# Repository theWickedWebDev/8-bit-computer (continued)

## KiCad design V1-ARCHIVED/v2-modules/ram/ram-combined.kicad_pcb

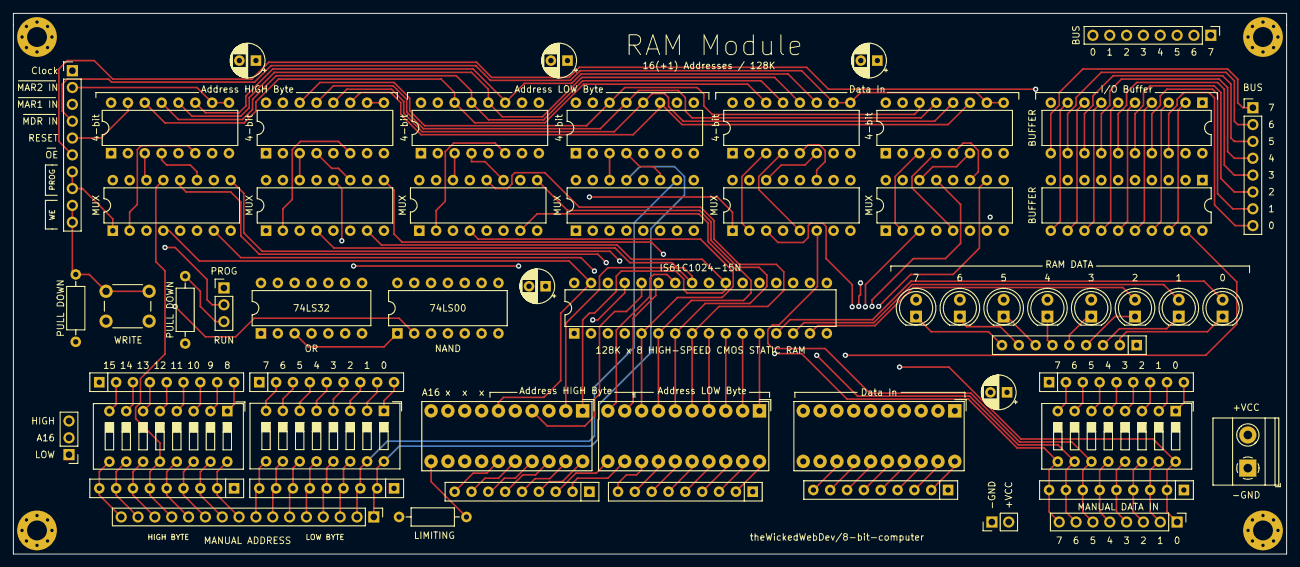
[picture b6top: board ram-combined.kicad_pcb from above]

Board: 4 copper layers, 192.0 x 81.5 mm, 59 parts (0 on the bottom side), 159 nets.

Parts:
BAR1, BAR2, BAR3: HDSP-4830_2; HDSP-4830
C1, C2, C3, C4, C5: CP1_Small; CP_Radial_D5.0mm_P2.50mm
D1, D2, D3, D4, D5, D6, D7, D8: LED; LED_D5.0mm
J1, J2, J8: Conn_01x08; PinHeader_1x08_P2.54mm_Vertical
J3: Conn_01x10; PinHeader_1x10_P2.54mm_Vertical
J4: Conn_01x02; PinHeader_1x02_P2.54mm_Vertical
J5: Screw_Terminal_01x02; TerminalBlock_Phoenix_MKDS-1,5-2_1x02_P5.00mm_Horizontal
J6: Conn_01x16; PinHeader_1x16_P2.54mm_Vertical
J7: Conn_01x08; PinHeader_1x03_P2.54mm_Vertical
R1, R2, R3: R_US; R_Axial_DIN0207_L6.3mm_D2.5mm_P10.16mm_Horizontal
RN1, RN2, RN3, RN4, RN5, RN6, RN7, RN8, RN9, RN10: R_Network08_US; R_Array_SIP9
SW1: SW_SPDT; PinHeader_1x03_P2.54mm_Vertical
SW2: SW_Push; SW_PUSH_6mm_H5mm
SW3, SW4, SW5: SW_DIP_x08; SW_DIP_SPSTx08_Slide_9.78x22.5mm_W7.62mm_P2.54mm
U1: 74LS00; DIP-14_W7.62mm
U2: 74LS32; DIP-14_W7.62mm
U3, U4, U6, U7, U15, U17: 74LS157; DIP-16_W7.62mm
U5, U8, U10, U12, U14, U16: 74LS173; DIP-16_W7.62mm
U9: IS61C1024-15N; DIP-32_W7.62mm
U11, U13: 74LS245; DIP-20_W7.62mm

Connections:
/A0: BAR2.1, U4.12, U9.12
/A1: BAR2.2, U4.9, U9.11
/A2: BAR2.3, U4.7, U9.10
/A3: BAR2.4, U4.4, U9.9
/A4: BAR2.5, U7.12, U9.8
/A5: BAR2.6, U7.9, U9.7
/A6: BAR2.7, U7.7, U9.6
/A7: BAR2.8, U7.4, U9.5
/A8: BAR2.9, U6.12, U9.27
/A9: BAR2.10, U6.9, U9.26
/A10: BAR1.1, U6.7, U9.23
/A11: BAR1.2, U6.4, U9.25
/A12: BAR1.3, U3.12, U9.4
/A13: BAR1.4, U3.9, U9.28
/A14: BAR1.5, U3.7, U9.3
/A15: BAR1.6, U3.4, U9.31
/IO0: D8.2, U9.13, U11.18, U13.2
/IO1: D7.2, U9.14, U11.17, U13.3
/IO2: D6.2, U9.15, U11.16, U13.4
/IO3: D5.2, U9.17, U11.15, U13.5
/IO4: D4.2, U9.18, U11.14, U13.6
/IO5: D3.2, U9.19, U11.13, U13.7
/IO6: D2.2, U9.20, U11.12, U13.8
/IO7: D1.2, U9.21, U11.11, U13.9
/MANUAL_DATA_00: J1.1, RN8.2, SW5.16, U17.3
/MANUAL_DATA_01: J1.2, RN8.3, SW5.15, U17.6
/MANUAL_DATA_02: J1.3, RN8.4, SW5.14, U17.10
/MANUAL_DATA_03: J1.4, RN8.5, SW5.13, U17.13
/MANUAL_DATA_04: J1.5, RN8.6, SW5.12, U15.3
/MANUAL_DATA_05: J1.6, RN8.7, SW5.11, U15.6
/MANUAL_DATA_06: J1.7, RN8.8, SW5.10, U15.10
/MANUAL_DATA_07: J1.8, RN8.9, SW5.9, U15.13
/MANUAL_MEM_ADR_00: J6.1, RN6.2, SW4.16, U4.13
/MANUAL_MEM_ADR_01: J6.2, RN6.3, SW4.15, U4.10
/MANUAL_MEM_ADR_02: J6.3, RN6.4, SW4.14, U4.6
/MANUAL_MEM_ADR_03: J6.4, RN6.5, SW4.13, U4.3
/MANUAL_MEM_ADR_04: J6.5, RN6.6, SW4.12, U7.13
/MANUAL_MEM_ADR_05: J6.6, RN6.7, SW4.11, U7.10
/MANUAL_MEM_ADR_06: J6.7, RN6.8, SW4.10, U7.6
/MANUAL_MEM_ADR_07: J6.8, RN6.9, SW4.9, U7.3
/MANUAL_MEM_ADR_08: J6.9, RN4.2, SW3.16, U6.13
/MANUAL_MEM_ADR_09: J6.10, RN4.3, SW3.15, U6.10
/MANUAL_MEM_ADR_10: J6.11, RN4.4, SW3.14, U6.6
/MANUAL_MEM_ADR_11: J6.12, RN4.5, SW3.13, U6.3
/MANUAL_MEM_ADR_12: J6.13, RN4.6, SW3.12, U3.13
/MANUAL_MEM_ADR_13: J6.14, RN4.7, SW3.11, U3.10
/MANUAL_MEM_ADR_14: J6.15, RN4.8, SW3.10, U3.6
/MANUAL_MEM_ADR_15: J6.16, RN4.9, SW3.9, U3.3
/MAR_00: U4.14, U12.3
/MAR_01: U4.11, U12.4
/MAR_02: U4.5, U12.5
/MAR_03: U4.2, U12.6
/MAR_04: U7.14, U10.3
/MAR_05: U7.11, U10.4
/MAR_06: U7.5, U10.5
/MAR_07: U7.2, U10.6
/MAR_08: U6.14, U8.3
/MAR_09: U6.11, U8.4
/MAR_10: U6.5, U8.5
/MAR_11: U6.2, U8.6
/MAR_12: U3.14, U5.3
/MAR_13: U3.11, U5.4
/MAR_14: U3.5, U5.5
/MAR_15: U3.2, U5.6
A16: BAR1.10, J7.2, U9.2
BUS_00: J2.8, J8.8, U8.14, U12.14, U13.18, U16.14
BUS_01: J2.7, J8.7, U8.13, U12.13, U13.17, U16.13
BUS_02: J2.6, J8.6, U8.12, U12.12, U13.16, U16.12
BUS_03: J2.5, J8.5, U8.11, U12.11, U13.15, U16.11
BUS_04: J2.4, J8.4, U5.14, U10.14, U13.14, U14.14
BUS_05: J2.3, J8.3, U5.13, U10.13, U13.13, U14.13
BUS_06: J2.2, J8.2, U5.12, U10.12, U13.12, U14.12
BUS_07: J2.1, J8.1, U5.11, U10.11, U13.11, U14.11
CLOCK: J3.1, U2.2, U5.7, U8.7, U10.7, U12.7, U14.7, U16.7
D0: BAR3.1, U11.2, U17.4
D1: BAR3.2, U11.3, U17.7
D2: BAR3.3, U11.4, U17.9
D3: BAR3.4, U11.5, U17.12
D4: BAR3.5, U11.6, U15.4
D5: BAR3.6, U11.7, U15.7
D6: BAR3.7, U11.8, U15.9
D7: BAR3.8, U11.9, U15.12
GND: C1.2, C2.2, C3.2, C4.2, C5.2, J4.1, J5.1, J7.1, R1.2, R2.2, R3.1, RN1.1, RN2.1, RN3.1, RN4.1, RN6.1, RN8.1, RN10.1, U1.7, U2.7, U3.8, U3.15, U4.8, U4.15, U5.1, U5.2, U5.8, U6.8, U6.15, U7.8, U7.15, U8.1, U8.2, U8.8, U9.16, U9.22, U9.24, U10.1, U10.2, U10.8, U11.10, U12.1, U12.2, U12.8, U13.10, U14.1, U14.2, U14.8, U15.8, U15.15, U16.1, U16.2, U16.8, U17.8, U17.15
MAR1_IN: J3.3, U10.9, U10.10, U12.9, U12.10
MAR2_IN: J3.2, U5.9, U5.10, U8.9, U8.10
MDR_IN: J3.4, U14.9, U14.10, U16.9, U16.10
unnamed: BAR1.11, R1.1
unnamed: BAR1.15, RN1.9
unnamed: BAR1.16, RN1.8
unnamed: BAR1.17, RN1.7
unnamed: BAR1.18, RN1.6
unnamed: BAR1.19, RN1.5
unnamed: BAR1.20, RN1.4
unnamed: BAR2.11, RN1.3
unnamed: BAR2.12, RN1.2
unnamed: BAR2.13, RN3.9
unnamed: BAR2.14, RN3.8
unnamed: BAR2.15, RN3.7
unnamed: BAR2.16, RN3.6
unnamed: BAR2.17, RN3.5
unnamed: BAR2.18, RN3.4
unnamed: BAR2.19, RN3.3
unnamed: BAR2.20, RN3.2
unnamed: BAR3.13, RN10.9
unnamed: BAR3.14, RN10.8
unnamed: BAR3.15, RN10.7
unnamed: BAR3.16, RN10.6
unnamed: BAR3.17, RN10.5
unnamed: BAR3.18, RN10.4
unnamed: BAR3.19, RN10.3
unnamed: BAR3.20, RN10.2
unnamed: D1.1, RN2.9
unnamed: D2.1, RN2.8
unnamed: D3.1, RN2.7
unnamed: D4.1, RN2.6
unnamed: D5.1, RN2.5
unnamed: D6.1, RN2.4
unnamed: D7.1, RN2.3
unnamed: D8.1, RN2.2
unnamed: R3.2, SW1.3
unnamed: RN5.2, SW3.8
unnamed: RN5.3, SW3.7
unnamed: RN5.4, SW3.6
unnamed: RN5.5, SW3.5
unnamed: RN5.6, SW3.4
unnamed: RN5.7, SW3.3
unnamed: RN5.8, SW3.2
unnamed: RN5.9, SW3.1
unnamed: RN7.2, SW4.8
unnamed: RN7.3, SW4.7
unnamed: RN7.4, SW4.6
unnamed: RN7.5, SW4.5
unnamed: RN7.6, SW4.4
unnamed: RN7.7, SW4.3
unnamed: RN7.8, SW4.2
unnamed: RN7.9, SW4.1
unnamed: RN9.2, SW5.8
unnamed: RN9.3, SW5.7
unnamed: RN9.4, SW5.6
unnamed: RN9.5, SW5.5
unnamed: RN9.6, SW5.4
unnamed: RN9.7, SW5.3
unnamed: RN9.8, SW5.2
unnamed: RN9.9, SW5.1
unnamed: U1.1, U2.3
unnamed: U1.3, U9.29, U11.19
unnamed: U14.3, U15.2
unnamed: U14.4, U15.5
unnamed: U14.5, U15.11
unnamed: U14.6, U15.14
unnamed: U16.3, U17.2
unnamed: U16.4, U17.5
unnamed: U16.5, U17.11
unnamed: U16.6, U17.14
OUTPUT_ENABLE: J3.6, U13.19
PROGRAM_MODE: J3.7, J3.8, SW1.2, U2.1, U3.1, U4.1, U6.1, U7.1, U15.1, U17.1
RESET: J3.5, U5.15, U8.15, U10.15, U12.15, U14.15, U16.15
VCC: C1.1, C2.1, C3.1, C4.1, C5.1, J4.2, J5.2, J7.3, RN5.1, RN7.1, RN9.1, SW1.1, SW2.2, U1.14, U2.14, U3.16, U4.16, U5.16, U6.16, U7.16, U8.16, U9.30, U9.32, U10.16, U11.1, U11.20, U12.16, U13.1, U13.20, U14.16, U15.16, U16.16, U17.16
WRITE_ENABLE: J3.9, J3.10, R2.1, SW2.1, U1.2

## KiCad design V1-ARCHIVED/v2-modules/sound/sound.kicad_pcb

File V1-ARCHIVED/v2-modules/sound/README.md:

# Sound / Audio Module

TODO: Description coming soon...

- FIXES
    - Adjust/rotate the pins for the audio-jack out - pin 1 is the large pin

### Sound 1 Module

<br/>

<br/>

<br/>

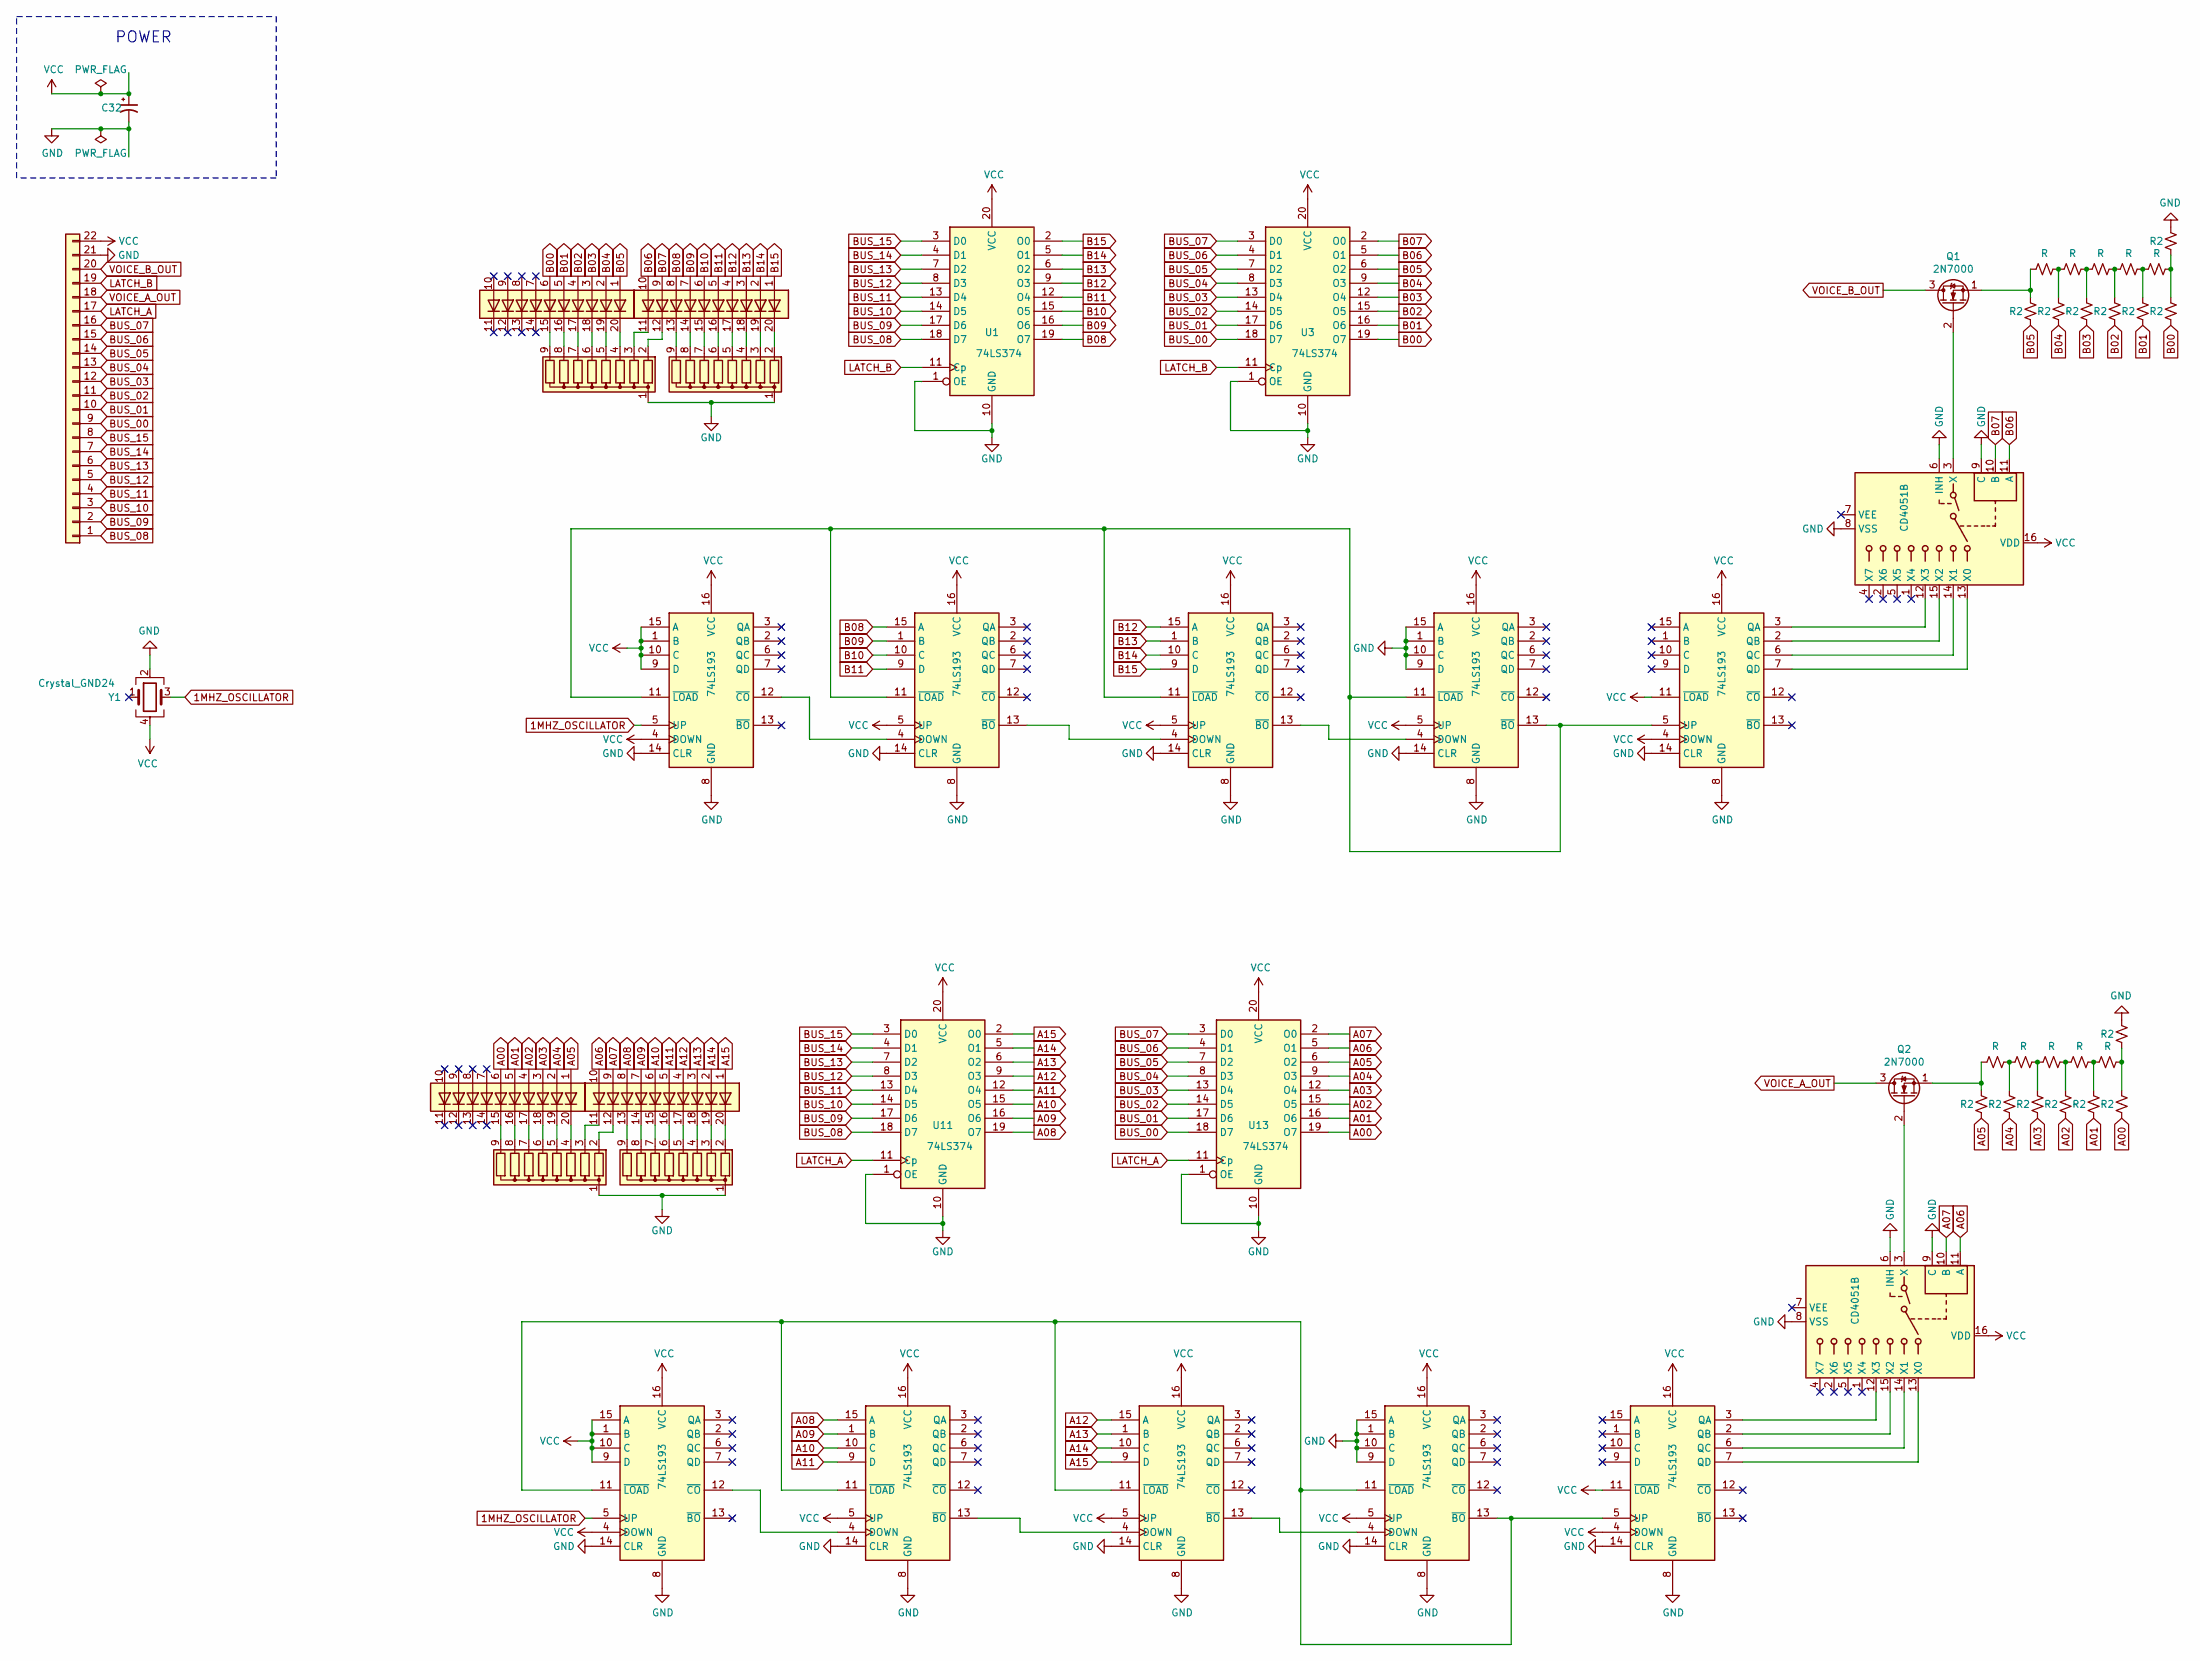
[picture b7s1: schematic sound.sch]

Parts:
BAR1, BAR2, BAR3, BAR4: HDSP-4830_2; HDSP-4830
C32: CP1_Small; CP_Radial_D5.0mm_P2.50mm
J69: Conn_01x22; PinSocket_1x22_P2.54mm_Horizontal
Q1, Q2: 2N7000; TO-92_Inline
R1, R2, R3, R4, R5, R6, R7, R8, R9, R10, R11, R12, R13, R14, R15, R16, R17, R18, R19, R20, R21, R22, R23, R24: R_Small_US; R_0805_2012Metric
RN1, RN2, RN3, RN4: R_Network08; R_Array_SIP9
U1, U3, U11, U13: 74LS374; DIP-20_W7.62mm
U2, U4, U5, U6, U7, U8, U10, U12, U14, U15: 74LS193; DIP-16_W7.62mm
U9, U16: CD4051B; DIP-16_W7.62mm
Y1: Crystal_GND24; full-can-14pin

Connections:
1MHZ_OSCILLATOR: U2.5 (UP), U5.5 (UP), Y1.3
A00: BAR3.6 (A), R24.1, U13.19 (O7)
A01: BAR3.5 (A), R21.1, U13.16 (O6)
A02: BAR3.4 (A), R19.1, U13.15 (O5)
A03: BAR3.3 (A), R17.1, U13.12 (O4)
A04: BAR3.2 (A), R15.1, U13.9 (O3)
A05: BAR3.1 (A), R13.1, U13.6 (O2)
A06: BAR4.10 (A), U13.5 (O1), U16.11 (A)
A07: BAR4.9 (A), U13.2 (O0), U16.10 (B)
A08: BAR4.8 (A), U7.15 (A), U11.19 (O7)
A09: BAR4.7 (A), U7.1 (B), U11.16 (O6)
A10: BAR4.6 (A), U7.10 (C), U11.15 (O5)
A11: BAR4.5 (A), U7.9 (D), U11.12 (O4)
A12: BAR4.4 (A), U11.9 (O3), U12.15 (A)
A13: BAR4.3 (A), U11.6 (O2), U12.1 (B)
A14: BAR4.2 (A), U11.5 (O1), U12.10 (C)
A15: BAR4.1 (A), U11.2 (O0), U12.9 (D)
B00: BAR1.6 (A), R1.1, U3.19 (O7)
B01: BAR1.5 (A), R4.1, U3.16 (O6)
B02: BAR1.4 (A), R6.1, U3.15 (O5)
B03: BAR1.3 (A), R8.1, U3.12 (O4)
B04: BAR1.2 (A), R10.1, U3.9 (O3)
B05: BAR1.1 (A), R12.1, U3.6 (O2)
B06: BAR2.10 (A), U3.5 (O1), U9.11 (A)
B07: BAR2.9 (A), U3.2 (O0), U9.10 (B)
B08: BAR2.8 (A), U1.19 (O7), U4.15 (A)
B09: BAR2.7 (A), U1.16 (O6), U4.1 (B)
B10: BAR2.6 (A), U1.15 (O5), U4.10 (C)
B11: BAR2.5 (A), U1.12 (O4), U4.9 (D)
B12: BAR2.4 (A), U1.9 (O3), U6.15 (A)
B13: BAR2.3 (A), U1.6 (O2), U6.1 (B)
B14: BAR2.2 (A), U1.5 (O1), U6.10 (C)
B15: BAR2.1 (A), U1.2 (O0), U6.9 (D)
BUS_00: J69.9, U3.18 (D7), U13.18 (D7)
BUS_01: J69.10, U3.17 (D6), U13.17 (D6)
BUS_02: J69.11, U3.14 (D5), U13.14 (D5)
BUS_03: J69.12, U3.13 (D4), U13.13 (D4)
BUS_04: J69.13, U3.8 (D3), U13.8 (D3)
BUS_05: J69.14, U3.7 (D2), U13.7 (D2)
BUS_06: J69.15, U3.4 (D1), U13.4 (D1)
BUS_07: J69.16, U3.3 (D0), U13.3 (D0)
BUS_08: J69.1, U1.18 (D7), U11.18 (D7)
BUS_09: J69.2, U1.17 (D6), U11.17 (D6)
BUS_10: J69.3, U1.14 (D5), U11.14 (D5)
BUS_11: J69.4, U1.13 (D4), U11.13 (D4)
BUS_12: J69.5, U1.8 (D3), U11.8 (D3)
BUS_13: J69.6, U1.7 (D2), U11.7 (D2)
BUS_14: J69.7, U1.4 (D1), U11.4 (D1)
BUS_15: J69.8, U1.3 (D0), U11.3 (D0)
GND: C32.2, J69.21, R2.1, R23.1, RN1.1 (common), RN2.1 (common), RN3.1 (common), RN4.1 (common), U1.1 (OE), U1.10 (GND), U2.8 (GND), U2.14 (CLR), U3.1 (OE), U3.10 (GND), U4.8 (GND), U4.14 (CLR), U5.8 (GND), U5.14 (CLR), U6.8 (GND), U6.14 (CLR), U7.8 (GND), U7.14 (CLR), U8.1 (B), U8.8 (GND), U8.9 (D), U8.10 (C), U8.14 (CLR), U8.15 (A), U9.6 (INH), U9.8 (VSS), U9.9 (C), U10.8 (GND), U10.14 (CLR), U11.1 (OE), U11.10 (GND), U12.8 (GND), U12.14 (CLR), U13.1 (OE), U13.10 (GND), U14.1 (B), U14.8 (GND), U14.9 (D), U14.10 (C), U14.14 (CLR), U14.15 (A), U15.8 (GND), U15.14 (CLR), U16.6 (INH), U16.8 (VSS), U16.9 (C), Y1.2
LATCH_A: J69.17, U11.11 (Cp), U13.11 (Cp)
LATCH_B: J69.19, U1.11 (Cp), U3.11 (Cp)
unnamed: BAR1.15 (K), RN1.9 (R8)
unnamed: BAR1.16 (K), RN1.8 (R7)
unnamed: BAR1.17 (K), RN1.7 (R6)
unnamed: BAR1.18 (K), RN1.6 (R5)
unnamed: BAR1.19 (K), RN1.5 (R4)
unnamed: BAR1.20 (K), RN1.4 (R3)
unnamed: BAR2.11 (K), RN1.3 (R2)
unnamed: BAR2.12 (K), RN1.2 (R1)
unnamed: BAR2.13 (K), RN2.9 (R8)
unnamed: BAR2.14 (K), RN2.8 (R7)
unnamed: BAR2.15 (K), RN2.7 (R6)
unnamed: BAR2.16 (K), RN2.6 (R5)
unnamed: BAR2.17 (K), RN2.5 (R4)
unnamed: BAR2.18 (K), RN2.4 (R3)
unnamed: BAR2.19 (K), RN2.3 (R2)
unnamed: BAR2.20 (K), RN2.2 (R1)
unnamed: BAR3.15 (K), RN3.9 (R8)
unnamed: BAR3.16 (K), RN3.8 (R7)
unnamed: BAR3.17 (K), RN3.7 (R6)
unnamed: BAR3.18 (K), RN3.6 (R5)
unnamed: BAR3.19 (K), RN3.5 (R4)
unnamed: BAR3.20 (K), RN3.4 (R3)
unnamed: BAR4.11 (K), RN3.3 (R2)
unnamed: BAR4.12 (K), RN3.2 (R1)
unnamed: BAR4.13 (K), RN4.9 (R8)
unnamed: BAR4.14 (K), RN4.8 (R7)
unnamed: BAR4.15 (K), RN4.7 (R6)
unnamed: BAR4.16 (K), RN4.6 (R5)
unnamed: BAR4.17 (K), RN4.5 (R4)
unnamed: BAR4.18 (K), RN4.4 (R3)
unnamed: BAR4.19 (K), RN4.3 (R2)
unnamed: BAR4.20 (K), RN4.2 (R1)
unnamed: Q1.1 (S), R11.2, R12.2
unnamed: Q1.2 (G), U9.3 (X)
unnamed: Q2.1 (S), R13.2, R14.2
unnamed: Q2.2 (G), U16.3 (X)
unnamed: R1.2, R2.2, R3.1
unnamed: R3.2, R4.2, R5.1
unnamed: R5.2, R6.2, R7.1
unnamed: R7.2, R8.2, R9.1
unnamed: R9.2, R10.2, R11.1
unnamed: R14.1, R15.2, R16.2
unnamed: R16.1, R17.2, R18.2
unnamed: R18.1, R19.2, R20.2
unnamed: R20.1, R21.2, R22.2
unnamed: R22.1, R23.2, R24.2
unnamed: U2.12 (~CO), U4.4 (DOWN)
unnamed: U4.13 (~BO), U6.4 (DOWN)
unnamed: U5.12 (~CO), U7.4 (DOWN)
unnamed: U6.13 (~BO), U8.4 (DOWN)
unnamed: U9.15 (X2), U10.2 (QB)
unnamed: U9.12 (X3), U10.3 (QA)
unnamed: U2.11 (~LOAD), U4.11 (~LOAD), U6.11 (~LOAD), U8.11 (~LOAD), U8.13 (~BO), U10.5 (UP)
unnamed: U9.14 (X1), U10.6 (QC)
unnamed: U9.13 (X0), U10.7 (QD)
unnamed: U7.13 (~BO), U12.4 (DOWN)
unnamed: U5.11 (~LOAD), U7.11 (~LOAD), U12.11 (~LOAD), U14.11 (~LOAD), U14.13 (~BO), U15.5 (UP)
unnamed: U12.13 (~BO), U14.4 (DOWN)
unnamed: U15.2 (QB), U16.15 (X2)
unnamed: U15.3 (QA), U16.12 (X3)
unnamed: U15.6 (QC), U16.14 (X1)
unnamed: U15.7 (QD), U16.13 (X0)
VCC: C32.1, J69.22, U1.20 (VCC), U2.1 (B), U2.4 (DOWN), U2.9 (D), U2.10 (C), U2.15 (A), U2.16 (VCC), U3.20 (VCC), U4.5 (UP), U4.16 (VCC), U5.1 (B), U5.4 (DOWN), U5.9 (D), U5.10 (C), U5.15 (A), U5.16 (VCC), U6.5 (UP), U6.16 (VCC), U7.5 (UP), U7.16 (VCC), U8.5 (UP), U8.16 (VCC), U9.16 (VDD), U10.4 (DOWN), U10.11 (~LOAD), U10.16 (VCC), U11.20 (VCC), U12.5 (UP), U12.16 (VCC), U13.20 (VCC), U14.5 (UP), U14.16 (VCC), U15.4 (DOWN), U15.11 (~LOAD), U15.16 (VCC), U16.16 (VDD), Y1.4
VOICE_A_OUT: J69.18, Q2.3 (D)
VOICE_B_OUT: J69.20, Q1.3 (D)

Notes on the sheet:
POWER

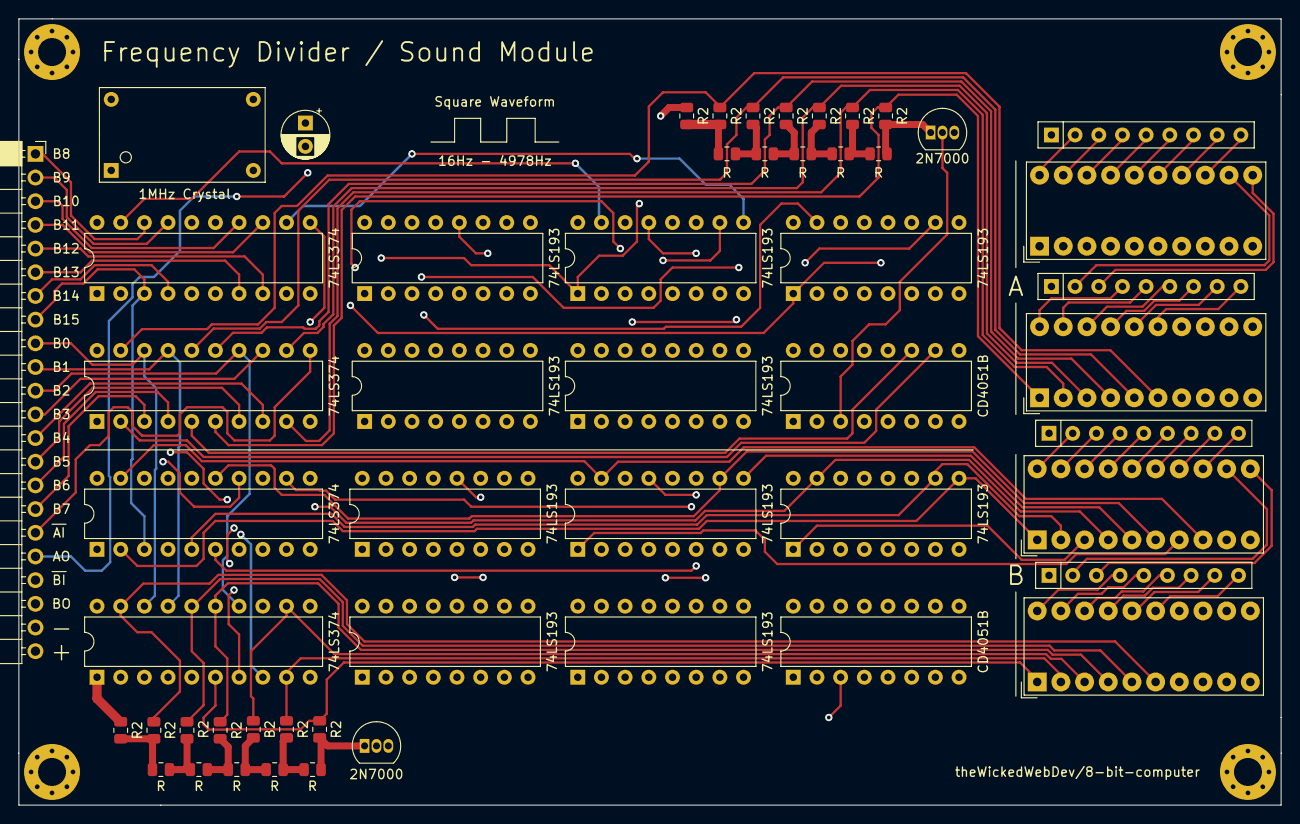
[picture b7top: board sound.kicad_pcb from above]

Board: 4 copper layers, 135.4 x 84.3 mm, 53 parts (0 on the bottom side), 117 nets.

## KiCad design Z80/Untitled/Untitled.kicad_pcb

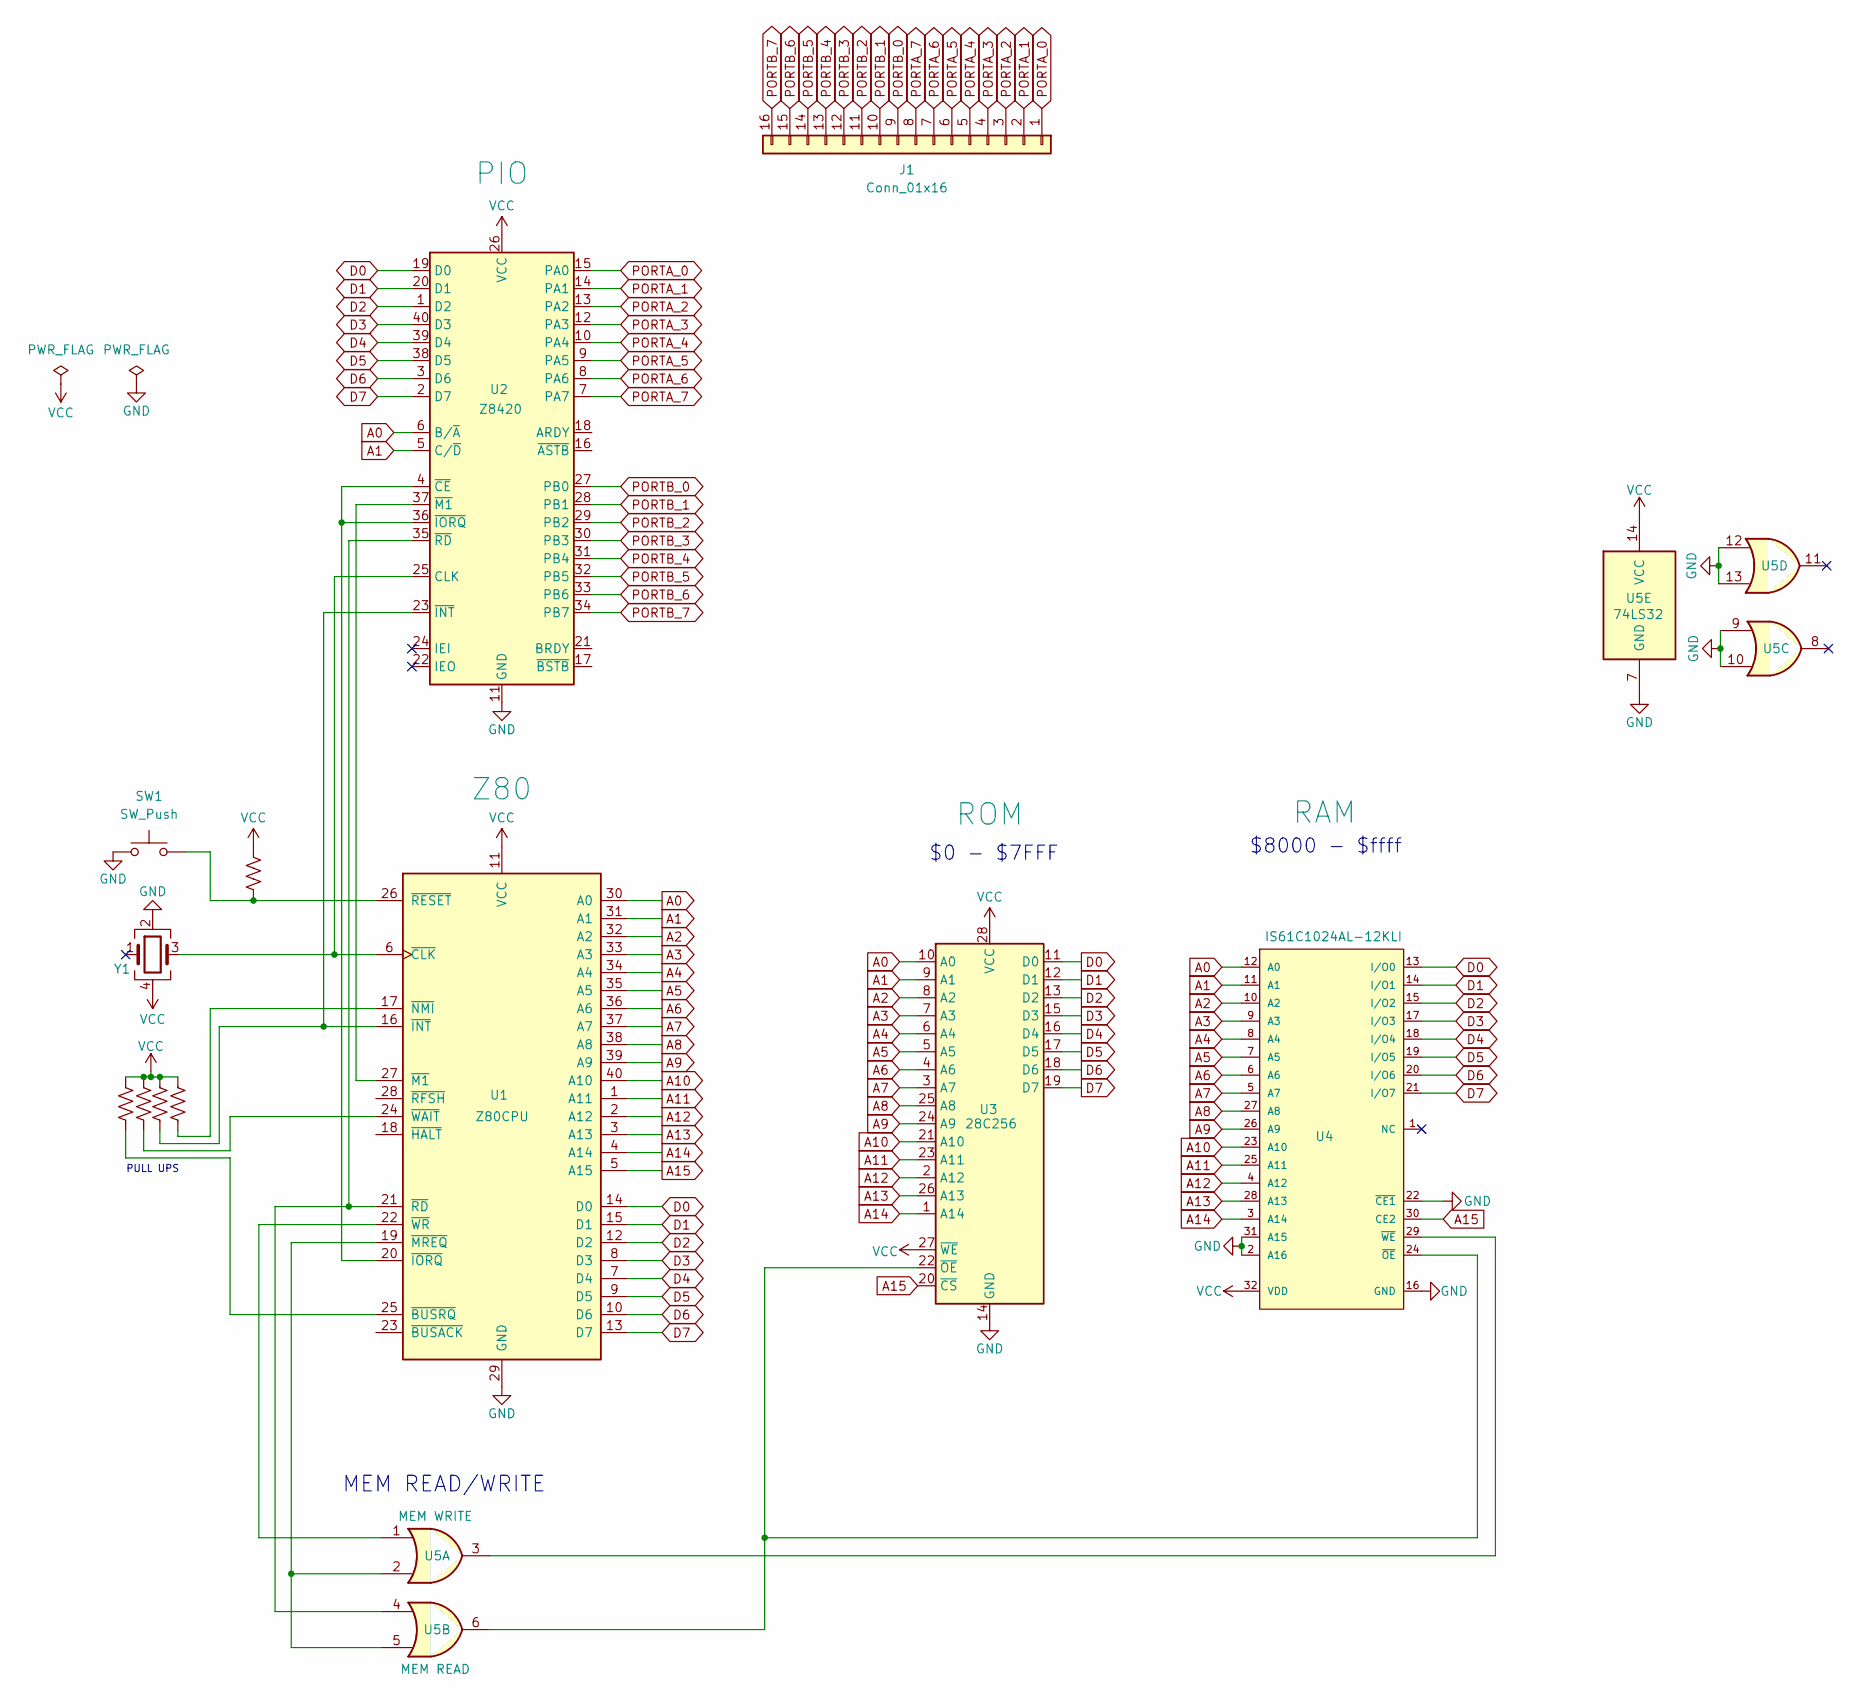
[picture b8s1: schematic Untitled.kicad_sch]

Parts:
J1: Conn_01x16; PinHeader_1x16_P2.54mm_Horizontal
R1, R2, R3, R4, R5: R_US; R_0805_2012Metric
SW1: SW_Push; SW_PUSH_6mm
U1: Z80CPU; DIP-40_W15.24mm
U2: Z8420; DIP-40_W15.24mm
U3: 28C256; DIP-28_W15.24mm_Socket
U4: IS61C1024AL-12KLI; DIP-32_W7.62mm
U5: 74LS32; TSSOP-14_4.4x5mm_P0.65mm
Y1: Crystal_GND24; Crystal_SMD_7050-4Pin_7.0x5.0mm

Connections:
A0: U1.30 (A0), U2.6 (B/~A), U3.10 (A0), U4.12 (A0)
A1: U1.31 (A1), U2.5 (C/~D), U3.9 (A1), U4.11 (A1)
A2: U1.32 (A2), U3.8 (A2), U4.10 (A2)
A3: U1.33 (A3), U3.7 (A3), U4.9 (A3)
A4: U1.34 (A4), U3.6 (A4), U4.8 (A4)
A5: U1.35 (A5), U3.5 (A5), U4.7 (A5)
A6: U1.36 (A6), U3.4 (A6), U4.6 (A6)
A7: U1.37 (A7), U3.3 (A7), U4.5 (A7)
A8: U1.38 (A8), U3.25 (A8), U4.27 (A8)
A9: U1.39 (A9), U3.24 (A9), U4.26 (A9)
A10: U1.40 (A10), U3.21 (A10), U4.23 (A10)
A11: U1.1 (A11), U3.23 (A11), U4.25 (A11)
A12: U1.2 (A12), U3.2 (A12), U4.4 (A12)
A13: U1.3 (A13), U3.26 (A13), U4.28 (A13)
A14: U1.4 (A14), U3.1 (A14), U4.3 (A14)
A15: U1.5 (A15), U3.20 (~CS), U4.30 (CE2)
D0: U1.14 (D0), U2.19 (D0), U3.11 (D0), U4.13 (I/O0)
D1: U1.15 (D1), U2.20 (D1), U3.12 (D1), U4.14 (I/O1)
D2: U1.12 (D2), U2.1 (D2), U3.13 (D2), U4.15 (I/O2)
D3: U1.8 (D3), U2.40 (D3), U3.15 (D3), U4.17 (I/O3)
D4: U1.7 (D4), U2.39 (D4), U3.16 (D4), U4.18 (I/O4)
D5: U1.9 (D5), U2.38 (D5), U3.17 (D5), U4.19 (I/O5)
D6: U1.10 (D6), U2.3 (D6), U3.18 (D6), U4.20 (I/O6)
D7: U1.13 (D7), U2.2 (D7), U3.19 (D7), U4.21 (I/O7)
GND: SW1.1, U1.29 (GND), U2.11 (GND), U3.14 (GND), U4.2 (A16), U4.16 (GND), U4.22 (~CE1), U4.31 (A15), U5.7 (GND), U5.9, U5.10, U5.12, U5.13, Y1.2
unnamed: U1.6 (~CLK), U2.25 (CLK), Y1.3
unnamed: R3.2, U1.16 (~INT), U2.23 (~INT)
unnamed: R4.2, U1.17 (~NMI)
unnamed: U1.19 (~MREQ), U5.2, U5.5
unnamed: U1.20 (~IORQ), U2.4 (~CE), U2.36 (~IORQ)
unnamed: U1.21 (~RD), U2.35 (~RD), U5.4
unnamed: U1.22 (~WR), U5.1
unnamed: R2.2, U1.24 (~WAIT)
unnamed: R1.2, U1.25 (~BUSRQ)
unnamed: R5.2, SW1.2, U1.26 (~RESET)
unnamed: U1.27 (~M1), U2.37 (~M1)
unnamed: U3.22 (~OE), U4.24 (~OE), U5.6
unnamed: U4.29 (~WE), U5.3
PORTA_0: J1.1, U2.15 (PA0)
PORTA_1: J1.2, U2.14 (PA1)
PORTA_2: J1.3, U2.13 (PA2)
PORTA_3: J1.4, U2.12 (PA3)
PORTA_4: J1.5, U2.10 (PA4)
PORTA_5: J1.6, U2.9 (PA5)
PORTA_6: J1.7, U2.8 (PA6)
PORTA_7: J1.8, U2.7 (PA7)
PORTB_0: J1.9, U2.27 (PB0)
PORTB_1: J1.10, U2.28 (PB1)
PORTB_2: J1.11, U2.29 (PB2)
PORTB_3: J1.12, U2.30 (PB3)
PORTB_4: J1.13, U2.31 (PB4)
PORTB_5: J1.14, U2.32 (PB5)
PORTB_6: J1.15, U2.33 (PB6)
PORTB_7: J1.16, U2.34 (PB7)
VCC: R1.1, R2.1, R3.1, R4.1, R5.1, U1.11 (VCC), U2.26 (VCC), U3.27 (~WE), U3.28 (VCC), U4.32 (VDD), U5.14 (VCC), Y1.4

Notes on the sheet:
$0 - $7FFF
$8000 - $ffff
PULL UPS
MEM READ/WRITE

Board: 2 copper layers, 13 parts (0 on the bottom side), 55 nets, no tracks yet.
